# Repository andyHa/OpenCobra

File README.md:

# OpenCobra
This is a collection of software and hardware which I build for my CNC (and maybe a 3D printer)

The main intention is to share Ideas and help others to overcome some pitfalls.

Eventually the project will consist of:
* A piece of software running on a Raspberry Pi (or the like) which provides a web interface to control the machine. 
* [A PIC24 based controller board](alig-board/README.md) which contains the stepper motor drivers, PWM controllers and some fancy control switches.
* The firmware which interprets the G-Code has the be built as well
* [An ICSP programmer](raspicsp/README.md) running on the Raspberry Pi which programs the PIC (yes that could be done using a bootloader, but
  ICSP via the Raspberry Pi can also do the initial programming without having to provide an additional ICSP socket on the already jammed board.

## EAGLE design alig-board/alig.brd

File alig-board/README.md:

# AliG-Board

This is the control board for the machine, based on a PIC24F. The current version is a very early and UNTESTED snapshot.
Further docs will follow once the board works as expected.

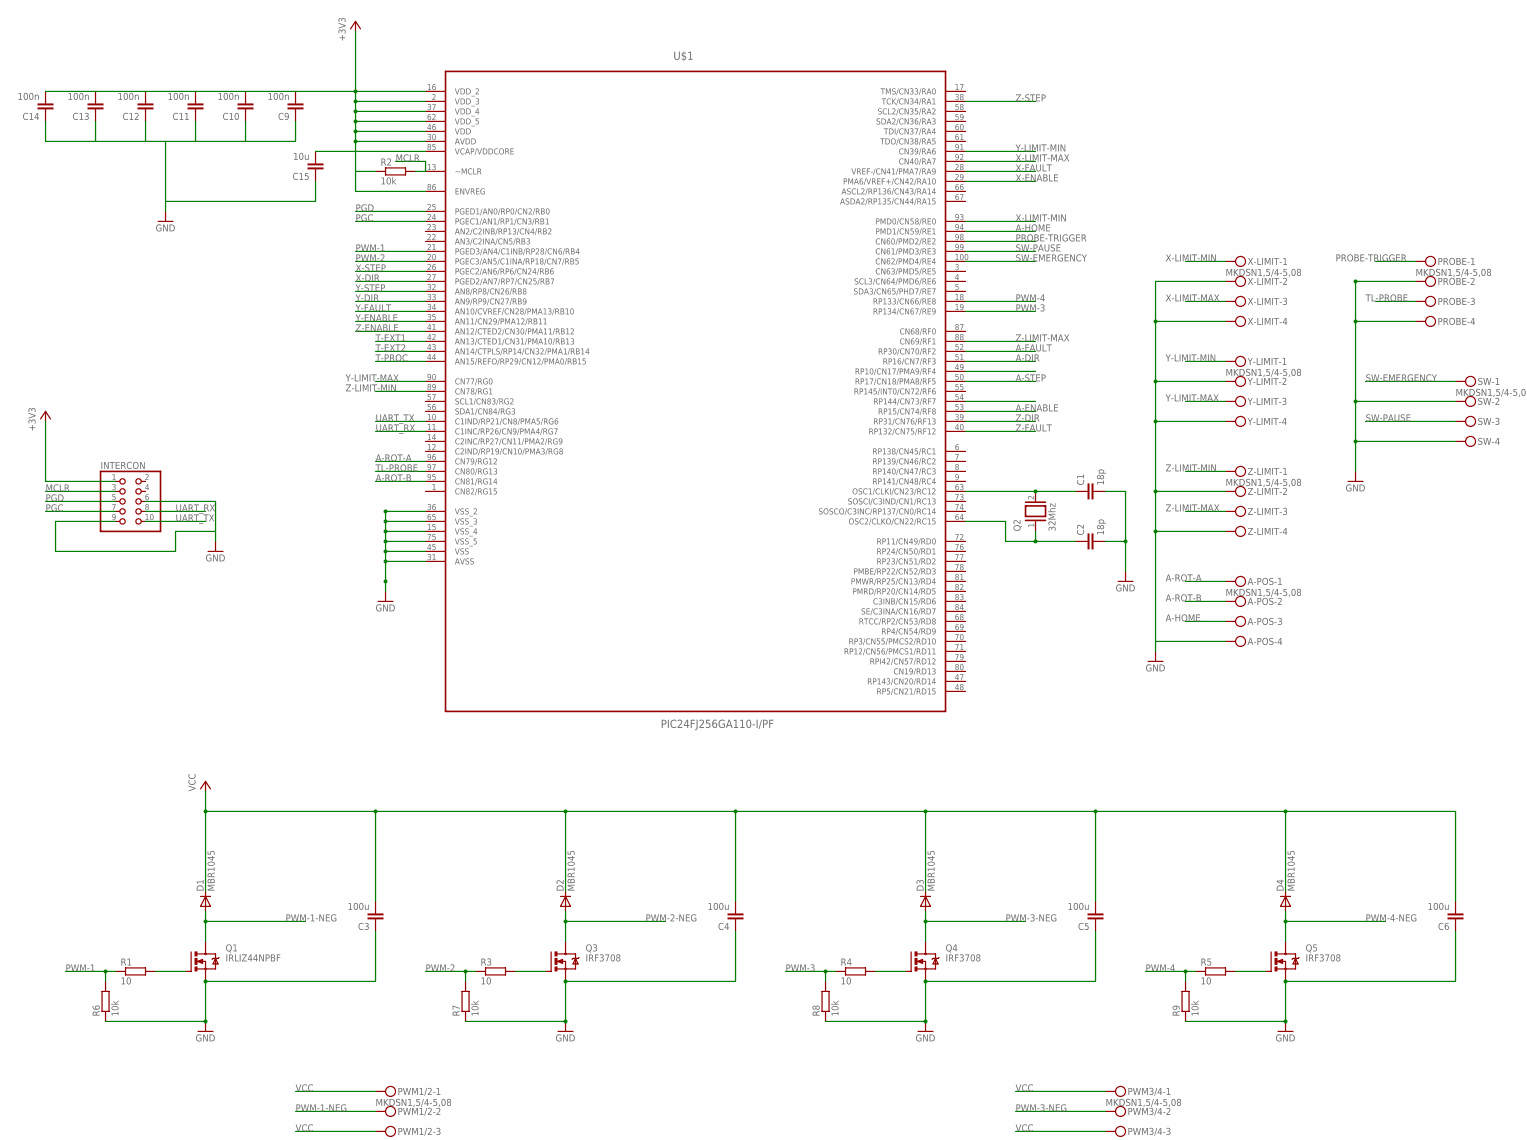
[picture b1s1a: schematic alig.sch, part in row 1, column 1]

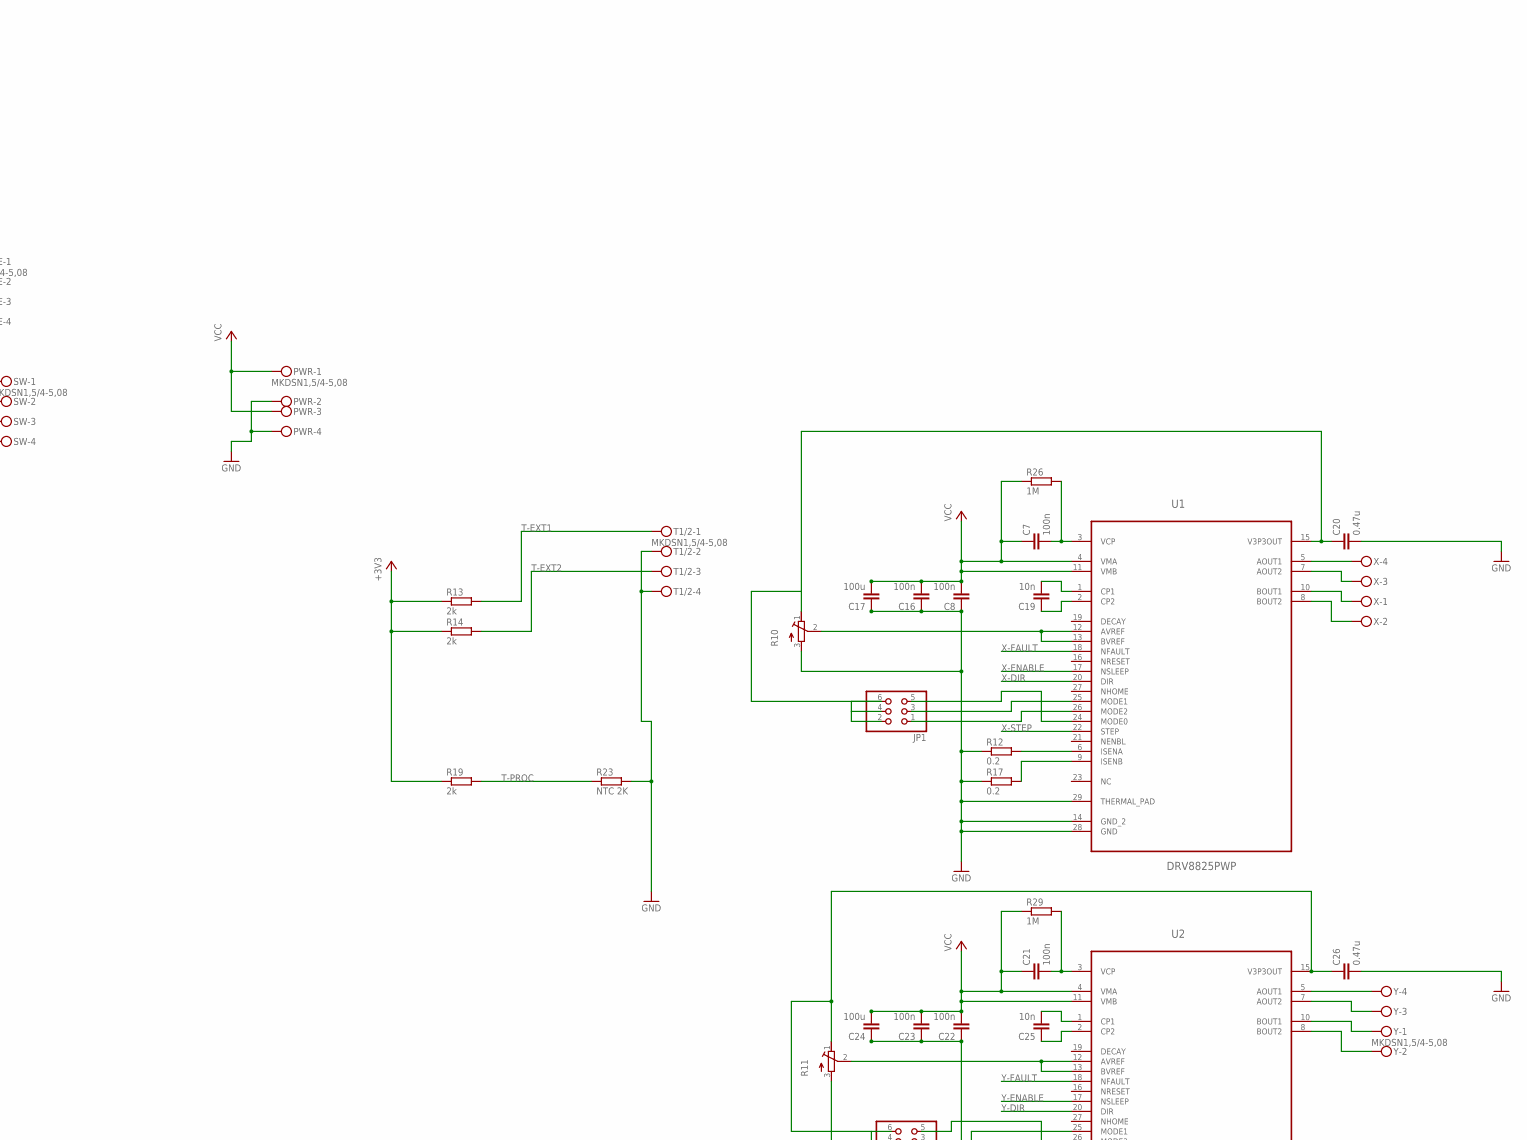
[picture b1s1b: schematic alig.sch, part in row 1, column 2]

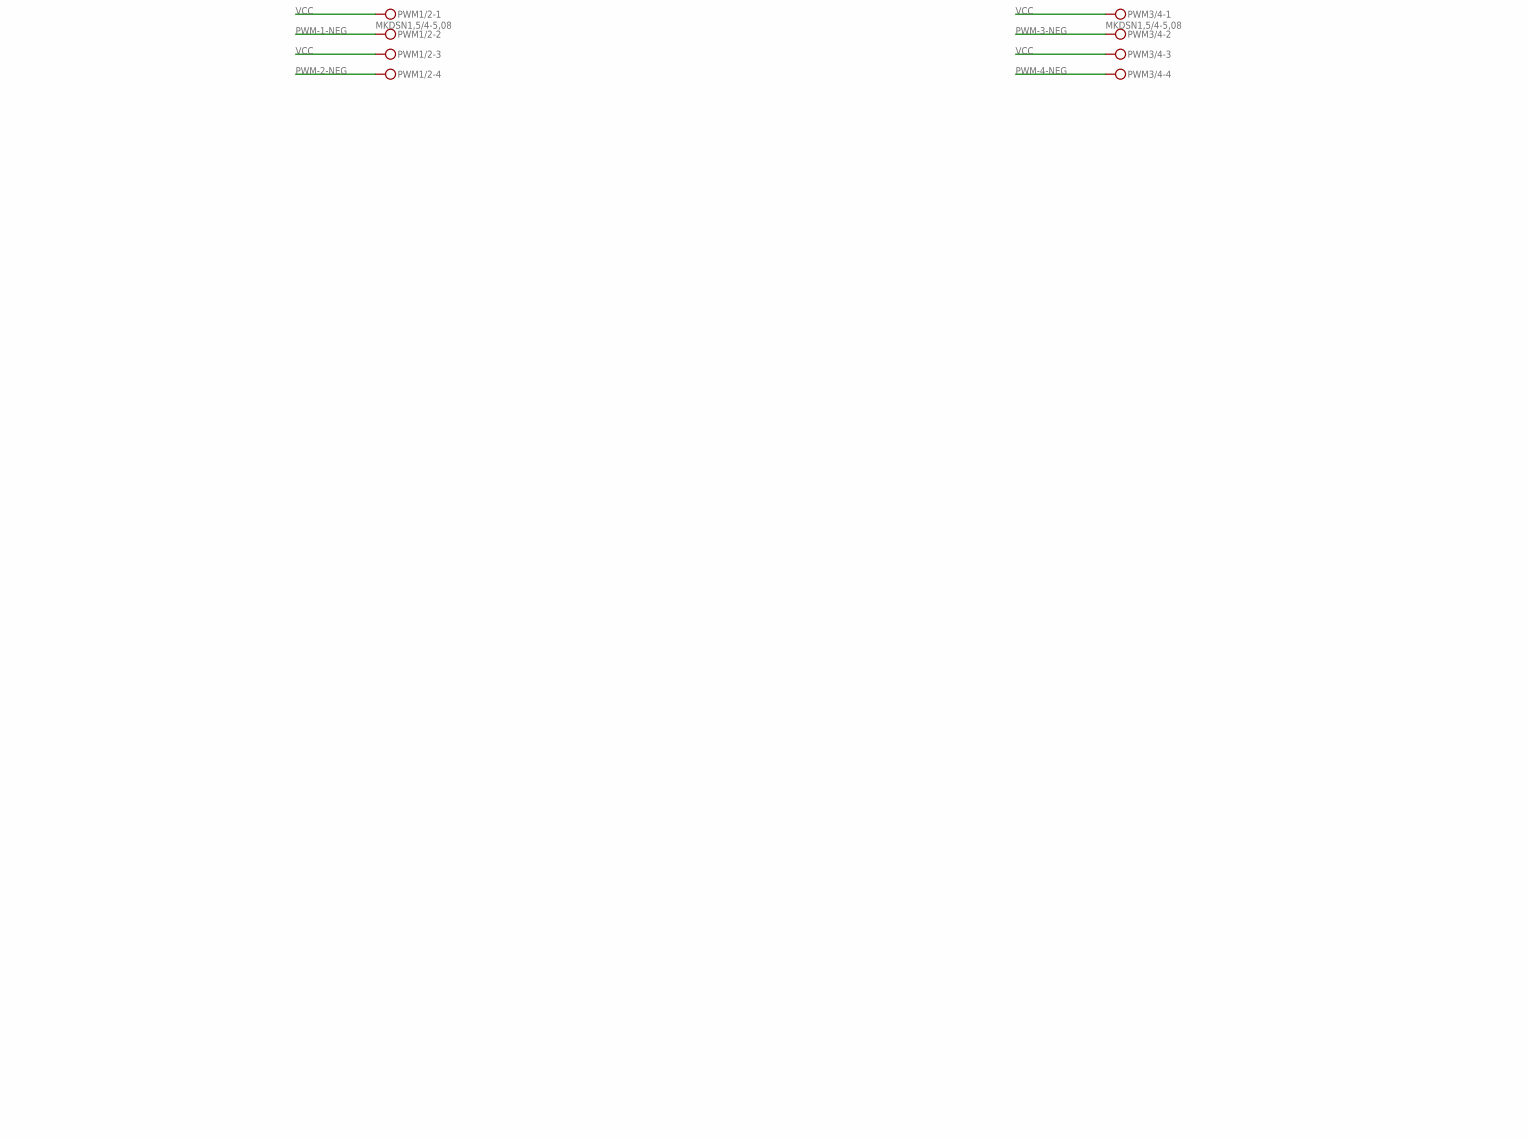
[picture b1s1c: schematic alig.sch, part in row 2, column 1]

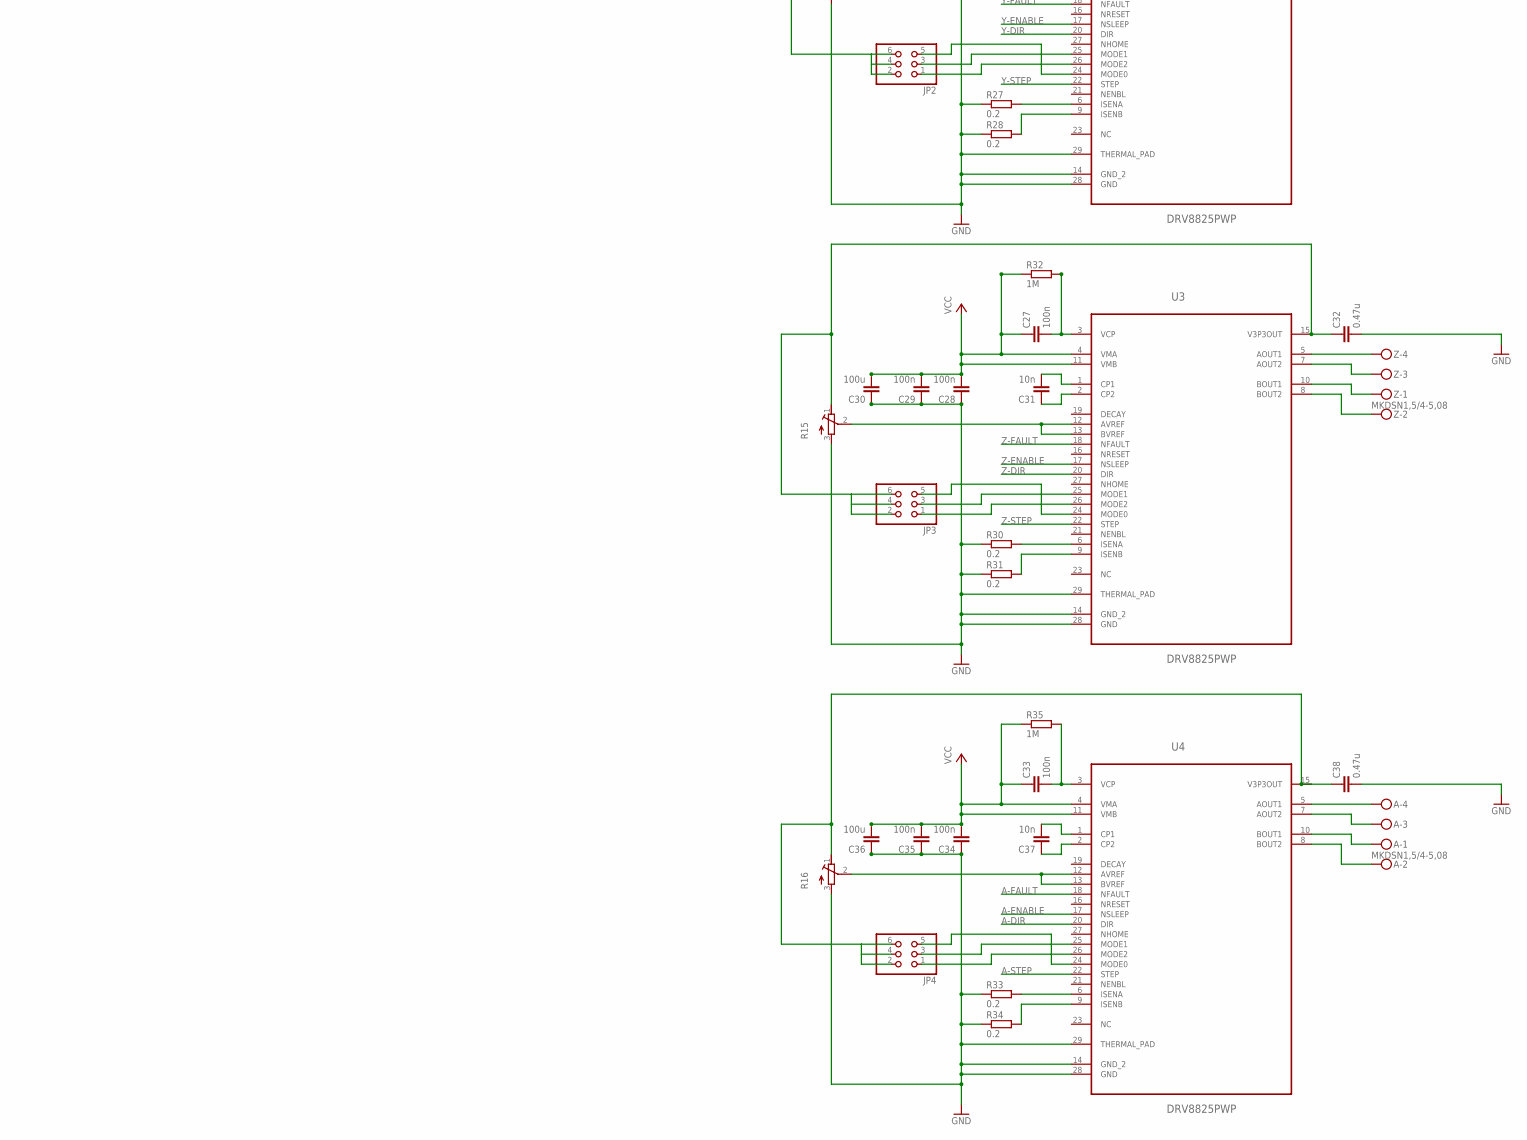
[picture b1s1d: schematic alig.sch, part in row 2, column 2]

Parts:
A: MKDSN1,5/4-5,08
A-POS: MKDSN1,5/4-5,08
C1, C2: 18p; C0805
C3, C4, C5, C6, C17, C24, C30, C36: 100u; C0805
C7, C8, C9, C10, C11, C12, C13, C14, C16, C21, C22, C23, C27, C28, C29, C33, C34, C35: 100n; C0805
C15: 10u; C0805
C19, C25, C31, C37: 10n; C0805
C20, C26, C32, C38: 0.47u; C0805
D1, D2, D3, D4: MBR1045; TO220ACS
INTERCON: PINHD-2X5; 2X05
JP1, JP2, JP3, JP4: PINHD-2X3; 2X03
PROBE: MKDSN1,5/4-5,08
PWM1/2, PWM3/4: MKDSN1,5/4-5,08
PWR: MKDSN1,5/4-5,08
Q1: IRLIZ44NPBF; TO220BV
Q2: 32Mhz; QS
Q3, Q4, Q5: IRF3708; TO220BV
R1, R3, R4, R5: 10; R0805
R2, R6, R7, R8, R9: 10k; R0805
R10, R11, R15, R16: R-TRIMM3314J; RTRIM3314J
R12, R17, R27, R28, R30, R31, R33, R34: 0.2; R1206
R13, R14, R19: 2k; R0805
R23: NTC 2K; R0805
R26, R29, R32, R35: 1M; R0805
SW: MKDSN1,5/4-5,08
T1/2: MKDSN1,5/4-5,08
U1, U2, U3, U4: DRV8825PWP; SOP65P640X120-29N
U$1: PIC24FJ256GA110-I/PF; QFP50P1600X1600X120-100N
X: MKDSN1,5/4-5,08
X-LIMIT: MKDSN1,5/4-5,08
Y: MKDSN1,5/4-5,08
Y-LIMIT: MKDSN1,5/4-5,08
Z: MKDSN1,5/4-5,08
Z-LIMIT: MKDSN1,5/4-5,08

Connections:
+3V3: C9.2, C10.2, C11.2, C12.2, C13.2, C14.2, INTERCON.1, R2.1, R13.1, R14.1, R19.1, U$1.2 (VDD_3), U$1.16 (VDD_2), U$1.30 (AVDD), U$1.37 (VDD_4), U$1.46 (VDD), U$1.62 (VDD_5), U$1.86 (ENVREG)
A-DIR: U4.20 (DIR), U$1.51 (RP16/CN7/RF3)
A-ENABLE: U4.17 (NSLEEP), U$1.53 (RP15/CN74/RF8)
A-FAULT: U4.18 (NFAULT), U$1.52 (RP30/CN70/RF2)
A-HOME: A-POS.3, U$1.94 (PMD1/CN59/RE1)
A-ROT-A: A-POS.1, U$1.96 (CN79/RG12)
A-ROT-B: A-POS.2, U$1.95 (CN81/RG14)
A-STEP: U4.22 (STEP), U$1.50 (RP17/CN18/PMA8/RF5)
AUX-IO-3: U$1.54 (RP144/CN73/RF7)
GND: A-POS.4, C1.2, C2.2, C3.1, C4.1, C5.1, C6.1, C8.1, C9.1, C10.1, C11.1, C12.1, C13.1, C14.1, C15.1, C16.1, C17.1, C20.2, C22.1, C23.1, C24.1, C26.2, C28.1, C29.1, C30.1, C32.2, C34.1, C35.1, C36.1, C38.2, INTERCON.6, INTERCON.9, PROBE.2, PROBE.4, PWR.2, PWR.4, Q1.S, Q3.S, Q4.S, Q5.S, R6.1, R7.1, R8.1, R9.1, R10.3 (A), R11.3 (A), R12.1, R15.3 (A), R16.3 (A), R17.1, R23.2, R27.1, R28.1, R30.1, R31.1, R33.1, R34.1, SW.2, SW.4, T1/2.2, T1/2.4, U1.14 (GND_2), U1.28 (GND), U1.29 (THERMAL_PAD), U2.14 (GND_2), U2.28 (GND), U2.29 (THERMAL_PAD), U3.14 (GND_2), U3.28 (GND), U3.29 (THERMAL_PAD), U4.14 (GND_2), U4.28 (GND), U4.29 (THERMAL_PAD), U$1.15 (VSS_4), U$1.31 (AVSS), U$1.36 (VSS_2), U$1.45 (VSS), U$1.65 (VSS_3), U$1.75 (VSS_5), X-LIMIT.2, X-LIMIT.4, Y-LIMIT.2, Y-LIMIT.4, Z-LIMIT.2, Z-LIMIT.4
MCLR: INTERCON.3, R2.2, U$1.13 (~MCLR)
unnamed: U1.5 (AOUT1), X.4
unnamed: Q3.G, R3.2
unnamed: Q4.G, R4.2
unnamed: C2.1, Q2.1, U$1.64 (OSC2/CLKO/CN22/RC15)
unnamed: C1.1, Q2.2, U$1.63 (OSC1/CLKI/CN23/RC12)
unnamed: C15.2, U$1.85 (VCAP/VDDCORE)
unnamed: Q1.G, R1.2
unnamed: Q5.G, R5.2
unnamed: U1.7 (AOUT2), X.3
unnamed: U1.10 (BOUT1), X.1
unnamed: U1.8 (BOUT2), X.2
unnamed: U2.5 (AOUT1), Y.4
unnamed: U2.7 (AOUT2), Y.3
unnamed: U2.10 (BOUT1), Y.1
unnamed: U2.8 (BOUT2), Y.2
unnamed: U3.5 (AOUT1), Z.4
unnamed: C21.2, R29.2, U2.3 (VCP)
unnamed: C25.2, U2.1 (CP1)
unnamed: C25.1, U2.2 (CP2)
unnamed: C7.2, R26.2, U1.3 (VCP)
unnamed: C26.1, JP2.2, JP2.4, JP2.6, R11.1 (E), U2.15 (V3P3OUT)
unnamed: C19.2, U1.1 (CP1)
unnamed: C19.1, U1.2 (CP2)
unnamed: JP2.1, U2.26 (MODE2)
unnamed: R27.2, U2.6 (ISENA)
unnamed: R12.2, U1.6 (ISENA)
unnamed: R17.2, U1.9 (ISENB)
unnamed: R28.2, U2.9 (ISENB)
unnamed: U3.7 (AOUT2), Z.3
unnamed: U3.10 (BOUT1), Z.1
unnamed: U3.8 (BOUT2), Z.2
unnamed: A.4, U4.5 (AOUT1)
unnamed: C27.2, R32.2, U3.3 (VCP)
unnamed: C31.2, U3.1 (CP1)
unnamed: C31.1, U3.2 (CP2)
unnamed: C32.1, JP3.2, JP3.4, JP3.6, R15.1 (E), U3.15 (V3P3OUT)
unnamed: R30.2, U3.6 (ISENA)
unnamed: R31.2, U3.9 (ISENB)
unnamed: A.3, U4.7 (AOUT2)
unnamed: A.1, U4.10 (BOUT1)
unnamed: A.2, U4.8 (BOUT2)
unnamed: R10.2 (S), U1.12 (AVREF), U1.13 (BVREF)
unnamed: C33.2, R35.2, U4.3 (VCP)
unnamed: C37.2, U4.1 (CP1)
unnamed: C37.1, U4.2 (CP2)
unnamed: C38.1, JP4.2, JP4.4, JP4.6, R16.1 (E), U4.15 (V3P3OUT)
unnamed: R33.2, U4.6 (ISENA)
unnamed: R34.2, U4.9 (ISENB)
unnamed: JP1.5, U1.24 (MODE0)
unnamed: R11.2 (S), U2.12 (AVREF), U2.13 (BVREF)
unnamed: R15.2 (S), U3.12 (AVREF), U3.13 (BVREF)
unnamed: R16.2 (S), U4.12 (AVREF), U4.13 (BVREF)
unnamed: JP1.3, U1.25 (MODE1)
unnamed: JP2.5, U2.24 (MODE0)
unnamed: JP1.1, U1.26 (MODE2)
unnamed: C20.1, JP1.2, JP1.4, JP1.6, R10.1 (E), U1.15 (V3P3OUT)
unnamed: JP2.3, U2.25 (MODE1)
unnamed: JP3.5, U3.24 (MODE0)
unnamed: JP3.3, U3.25 (MODE1)
unnamed: JP3.1, U3.26 (MODE2)
unnamed: JP4.5, U4.24 (MODE0)
unnamed: JP4.3, U4.25 (MODE1)
unnamed: JP4.1, U4.26 (MODE2)
PGC: INTERCON.7, U$1.24 (PGEC1/AN1/RP1/CN3/RB1)
PGD: INTERCON.5, U$1.25 (PGED1/AN0/RP0/CN2/RB0)
PROBE-TRIGGER: PROBE.1, U$1.98 (CN60/PMD2/RE2)
PWM-1: R1.1, R6.2, U$1.21 (PGED3/AN4/C1INB/RP28/CN6/RB4)
PWM-1-NEG: D1.A, PWM1/2.2, Q1.D
PWM-2: R3.1, R7.2, U$1.20 (PGEC3/AN5/C1INA/RP18/CN7/RB5)
PWM-2-NEG: D2.A, PWM1/2.4, Q3.D
PWM-3: R4.1, R8.2, U$1.19 (RP134/CN67/RE9)
PWM-3-NEG: D3.A, PWM3/4.2, Q4.D
PWM-4: R5.1, R9.2, U$1.18 (RP133/CN66/RE8)
PWM-4-NEG: D4.A, PWM3/4.4, Q5.D
SW-EMERGENCY: SW.1, U$1.100 (CN62/PMD4/RE4)
SW-PAUSE: SW.3, U$1.99 (CN61/PMD3/RE3)
T-EXT1: R13.2, T1/2.1, U$1.42 (AN13/CTED1/CN31/PMA10/RB13)
T-EXT2: R14.2, T1/2.3, U$1.43 (AN14/CTPLS/RP14/CN32/PMA1/RB14)
T-PROC: R19.2, R23.1, U$1.44 (AN15/REFO/RP29/CN12/PMA0/RB15)
TL-PROBE: PROBE.3, U$1.97 (CN80/RG13)
UART_RX: INTERCON.8, U$1.11 (C1INC/RP26/CN9/PMA4/RG7)
UART_TX: INTERCON.10, U$1.10 (C1IND/RP21/CN8/PMA5/RG6)
VCC: C3.2, C4.2, C5.2, C6.2, C7.1, C8.2, C16.2, C17.2, C21.1, C22.2, C23.2, C24.2, C27.1, C28.2, C29.2, C30.2, C33.1, C34.2, C35.2, C36.2, D1.C, D2.C, D3.C, D4.C, PWM1/2.1, PWM1/2.3, PWM3/4.1, PWM3/4.3, PWR.1, PWR.3, R26.1, R29.1, R32.1, R35.1, U1.4 (VMA), U1.11 (VMB), U2.4 (VMA), U2.11 (VMB), U3.4 (VMA), U3.11 (VMB), U4.4 (VMA), U4.11 (VMB)
X-DIR: U1.20 (DIR), U$1.27 (PGED2/AN7/RP7/CN25/RB7)
X-ENABLE: U1.17 (NSLEEP), U$1.29 (PMA6/VREF+/CN42/RA10)
X-FAULT: U1.18 (NFAULT), U$1.28 (VREF-/CN41/PMA7/RA9)
X-LIMIT-MAX: U$1.92 (CN40/RA7), X-LIMIT.3
X-LIMIT-MIN: U$1.93 (PMD0/CN58/RE0), X-LIMIT.1
X-STEP: U1.22 (STEP), U$1.26 (PGEC2/AN6/RP6/CN24/RB6)
Y-DIR: U2.20 (DIR), U$1.33 (AN9/RP9/CN27/RB9)
Y-ENABLE: U2.17 (NSLEEP), U$1.35 (AN11/CN29/PMA12/RB11)
Y-FAULT: U2.18 (NFAULT), U$1.34 (AN10/CVREF/CN28/PMA13/RB10)
Y-LIMIT-MAX: U$1.90 (CN77/RG0), Y-LIMIT.3
Y-LIMIT-MIN: U$1.91 (CN39/RA6), Y-LIMIT.1
Y-STEP: U2.22 (STEP), U$1.32 (AN8/RP8/CN26/RB8)
Z-DIR: U3.20 (DIR), U$1.39 (RP31/CN76/RF13)
Z-ENABLE: U3.17 (NSLEEP), U$1.41 (AN12/CTED2/CN30/PMA11/RB12)
Z-FAULT: U3.18 (NFAULT), U$1.40 (RP132/CN75/RF12)
Z-LIMIT-MAX: U$1.88 (CN69/RF1), Z-LIMIT.3
Z-LIMIT-MIN: U$1.89 (CN78/RG1), Z-LIMIT.1
Z-STEP: U3.22 (STEP), U$1.38 (TCK/CN34/RA1)
ZTL-PROBE: U$1.49 (RP10/CN17/PMA9/RF4)

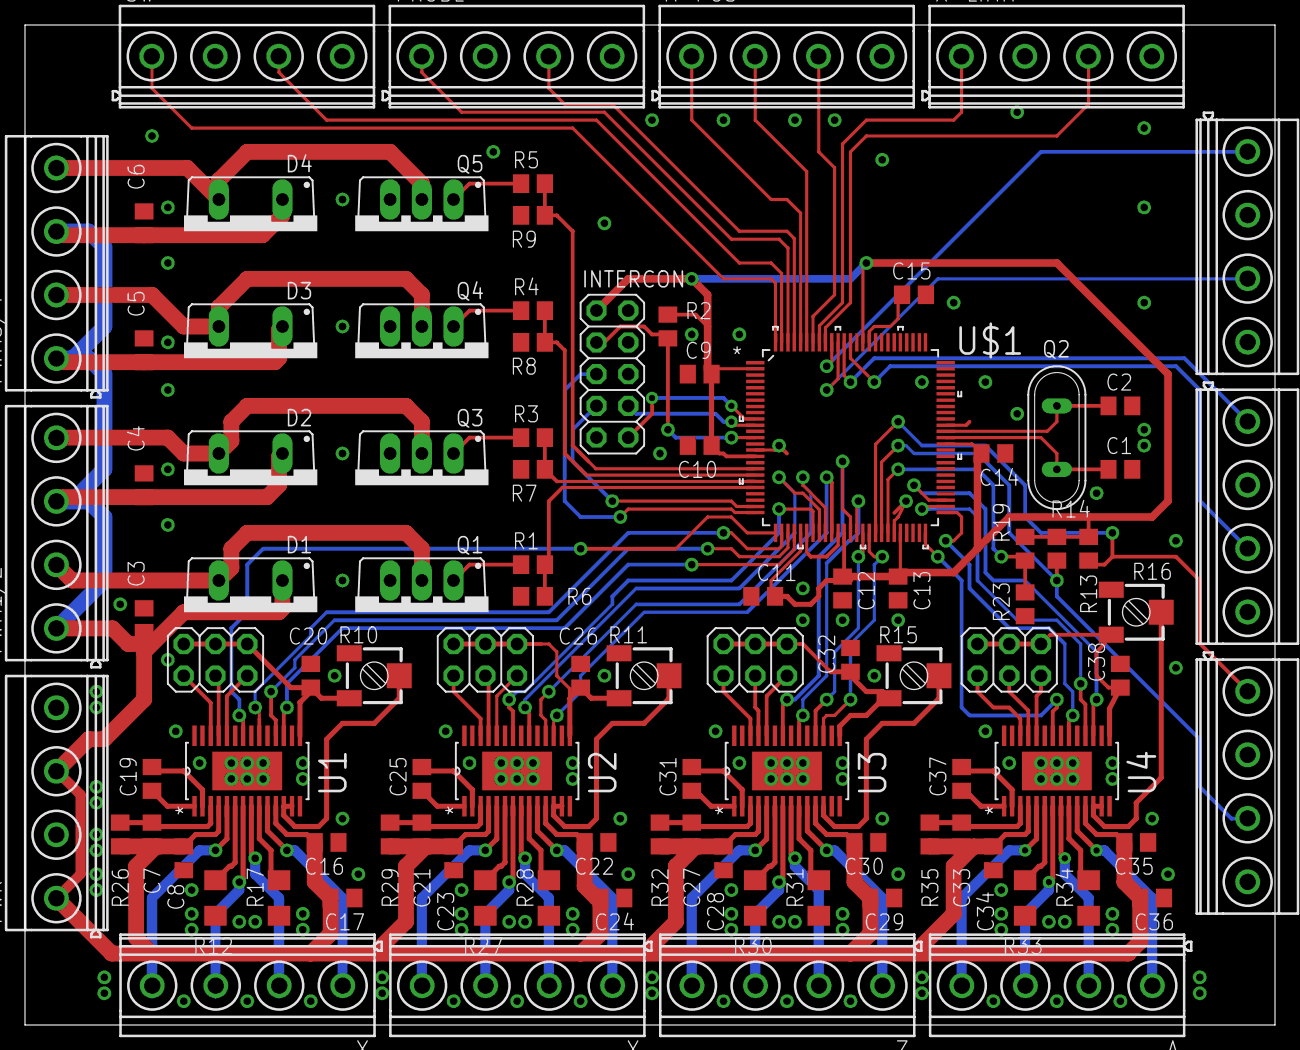
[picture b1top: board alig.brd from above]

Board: 2 copper layers, 100.0 x 80.0 mm, 99 parts (0 on the bottom side), 111 nets.

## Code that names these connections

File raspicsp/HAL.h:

//
// Defines the hardware abstraction layer.
//

#ifndef RASPICSP_HAL_H
#define RASPICSP_HAL_H

#include <stdint.h>

/*
 * The Hardware Abstraction Layer contains raspberry PI specific code to drive the
 * GPIO pins in order to behave as required for the pins MCLR (reset pin), PGC (clock), PGD (data).
 */
class HAL {
private:

    static const uint32_t BCM2708_PERI_BASE = 0x20000000;
    static const uint32_t GPIO_BASE = BCM2708_PERI_BASE + 0x200000;
    static const uint32_t BLOCK_SIZE = 4096;
    static const uint32_t PERIOD_MICRO_SECONDS = 1;

    uint8_t mclr_pin;
    uint8_t pgd_pin;
    uint8_t pgc_pin;
    volatile unsigned *gpio;

    /*
     * Maps the GPIO pins into the address space of our process to gain control
     */
    void setup_io();

    /*
     * Initializes the GPIO pins as required
     */
    void setup_pins();

    /*
     * Makes the given pin an input pin
     */
    void make_input(uint8_t pin);

    /*
     * Makes the given pin an output pin
     */
    void make_output(uint8_t pin);

    /*
     * Writes a 1 (high) to the given pin
     */
    void set_pin(uint8_t pin);

    /*
     * Writes a 0 (low) to the given pin
     */
    void clear_pin(uint8_t pin);

    /*
     * Reads the value of the given pin
     */
    int read_pin(uint8_t pin);

    /*
     * Delays the execution my the given number of microseconds
     */
    void delayMicrosecondsHard(unsigned int howLong);

public:

    /*
     * Creates a new instance which uses the given GPIOs as MCLR, PGD und PGC
     */
    HAL(uint8_t mclr_pin, uint8_t pgd_pin, uint8_t pgc_pin);

    /*
     * Raises the reset pin to 1
     */
    void mclr_up();

    /*
     * Lowers the reset pin to 0
     */
    void mclr_down();

    /*
     * Enables write mode (PCD is an output)
     */
    void write_mode();

    /*
     * Enables read mode (PGD is an input)
     */
    void read_mode();

    /*
     * Writes a bit (sets PGD to 0 or 1 depending on bit and emits a plus on PGC).
     */
    void write_bit(int bit);

    /*
     * Reads a bit (reads PCD while sending a pulse on PGC)
     */
    int read_bit();

};


#endif //RASPICSP_HAL_H

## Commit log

2016-04-11 Added initial board designs
2016-04-11 Update README.md
    Fixed link
